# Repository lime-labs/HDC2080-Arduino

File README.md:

Texas Instruments HDC2080 Arduino Library
==========================================
*** NOTE: This library was originally from https://training.ti.com/how-interface-hdc2010-humidity-and-temperature-sensor-arduino-using-i2c
*** This library was originally for the HDC2010 and was converted to support the HDC2080.
*** forked from https://github.com/tinkeringtech/HDC2080_breakout to https://github.com/lime-labs/HDC2080-Arduino for use in the "Lime Labs Hot Slice" temperature and humidity logger project
*** contains fixes and cleanups generously provided by https://github.com/stickbreaker to fix behavior on newer ESP32 Arduino core releases
*** generalized the error handling to restore compatibilty with broader range of MCUs and Arduino cores.

Description: 
	The HDC2080 Library for Arduino allows for configuration and use of 
	the HDC2080 without the need to use I2C or know the register mapping of 
	the device. 
	
	Feel free to modify and reuse this library as you see fit. This code is
	released AS-IS into the public domain. No guarantee or warranty is given.
	This code will not be supported by Texas Instruments after release. 
	
---------------------------------------------------------------------------------------
Installation:
	Extract or copy the HDC2080 Arduino Library folder into the 'libraries'
	folder found in your Arduino Sketchbook. The example sketch will then
	be available under 'custom libraries' when you select File-> Examples.
	
---------------------------------------------------------------------------------------
Contents:
	HDC2080.cpp 		- C++ File defining  behavior of HDC2080 methods
	HDC2080.h   		- Header file for HDC2080.cpp
	keywords.txt		- Keywords from HDC2080.h
	library.properties 	- Properties file for HDC2080 library
	Examples 		- Holds HDC2080 example sketch

----------------------------------------------------------------------------------------

Library Functions:

		HDC2080(uint8_t addr)
			- Initializes an HDC2080 object
			
		void begin(void)  						
			- Equivalent to wire.Begin(), Joins I2C Bus
   
                bool isConnected(void)
		        - Returns true if sensor is connected
			
		float readTemp(void)					
			- Returns the temperature in degrees C
		
		float readHumidity(void)				
			- Returns the relative humidity
		
		void enableHeater(void)				
			- Enables the heating element
		
		void disableHeater(void)
			- Disables the heating element
			
		void setLowTemp(float temp)			
			- Sets the lower temperature threshold (in celcius). Temperature may not
			  be exact due to 8 bit quantization.
			  
		void setHighTemp(float temp)	
			- Sets the upper temperature threshold (in celcius). Temperature may not
			  be exact due to 8 bit quantization.	
			  
		void setHighHumidity(float humid)		
			- Sets the upper humidity threshold (as a %). Humidity may not
			  be exact due to 8 bit quantization.
		
		void setLowHumidity(float humid)	
			- Sets the lower humidity threshold (as a %). Humidity may not
			  be exact due to 8 bit quantization.
	
		float readLowHumidityThreshold(void)	
			- Returns contents of low humidity threshold register
			
		float readHighHumidityThreshold(void)	
			- Returns contents of high humidity threshold register
			
		float readLowTempThreshold(void)		
			- Returns contents of low temperature threshold register (in C)
			
		float readHighTempThreshold(void)
			- Returns contents of high temperature threshold register (in C)
			
		void triggerMeasurement(void)			
			- Triggers a manual temperature/humidity reading. Use to start
			  the taking of regular measurements.
			  
		void reset(void)						
			- Triggers a software reset, all registers are returned to default values
			
		void enableInterrupt(void)				
			- Enables the interrupt/DRDY pin
			
		void disableInterrupt(void)			
			- Disables the interrupt/DRDY pin (High Z)

		uint8_t readInterruptStatus(void)		
			- Reads the status of the interrupt register. The results can be interpreted
			  to know which interrupts have been generated. The HDC2010 datasheet explains
			  the contents of this register.
			  
		void clearMaxTemp(void)			
			- Clears the Maximum temperature register.
			
		void clearMaxHumidity(void)			
			- Clears the Maximum humidity register
			
		float readMaxTemp(void) 				
			- Reads the maximum temperature register
			
		float readMaxHumidity(void)			
			- Reads the maximum humidity register
			
		void enableThresholdInterrupt(void)	
			- Enables high and low temperature/humidity interrupts
			
		void disableThresholdInterrupt(void)	
			- Disables high and low temperature/humidity interrupts
			
		void enableDRDYInterrupt(void)		
			- Enables data ready interrupt
			
		void disableDRDYInterrupt(void)		
			- Disables data ready interrupt
		
		uint8_t readTempOffsetAdjust(void)
			- Returns the offset adjust in binary
		
		uint8_t setTempOffsetAdjust(uint8_t)
			- Set and return the offset adjust in binary

		uint8_t readHumidityOffsetAdjust(void)
			- Returns the offset adjust in binary

		uint8_t setHumidityOffsetAdjust(uint8_t)
			- Set and return the offset adjust in binary

		void setTempRes(int resolution)		
		void setHumidRes(int resolution)	
		   Sets Temperature & Humidity Resolution, 3 options
		   0 - 14 bit
		   1 - 11 bit
		   2 - 9 bit
		   default - 14 bit	

		void setTempRes(int resolution)		
		void setHumidRes(int resolution)	
		   Sets Temperature & Humidity Resolution, 3 options
		   0 - 14 bit
		   1 - 11 bit
		   2 - 9 bit
		   default - 14 bit	

		void setMeasurementMode(int mode)
		   Sets measurement mode, 3 options
		   0 - Temperature and Humidity
		   1 - Temperature only
		   2 - Humidity only
		   default - Temperature & Humidity	

		void setRate(int rate)
		   Sets reading rate, 8 options
		   0 - Manual
		   1 - reading every 2 minutes
		   2 - reading every minute
		   3 - reading every ten seconds
		   4 - reading every 5 seconds
		   5 - reading every second
		   6 - reading at 2Hz
		   7 - reading at 5Hz
		   default - Manual			

		void setInterruptPolarity(int polarity)
		   Sets Interrupt polarity, 2 options
		   0 - Active Low
		   1 - Active High
		   default - Active Low		

		void setInterruptMode(int polarity)
		   Sets Interrupt mode, 2 options
		   0 - Level sensitive
		   1 - Comparator mode
		   default - Level sensitive

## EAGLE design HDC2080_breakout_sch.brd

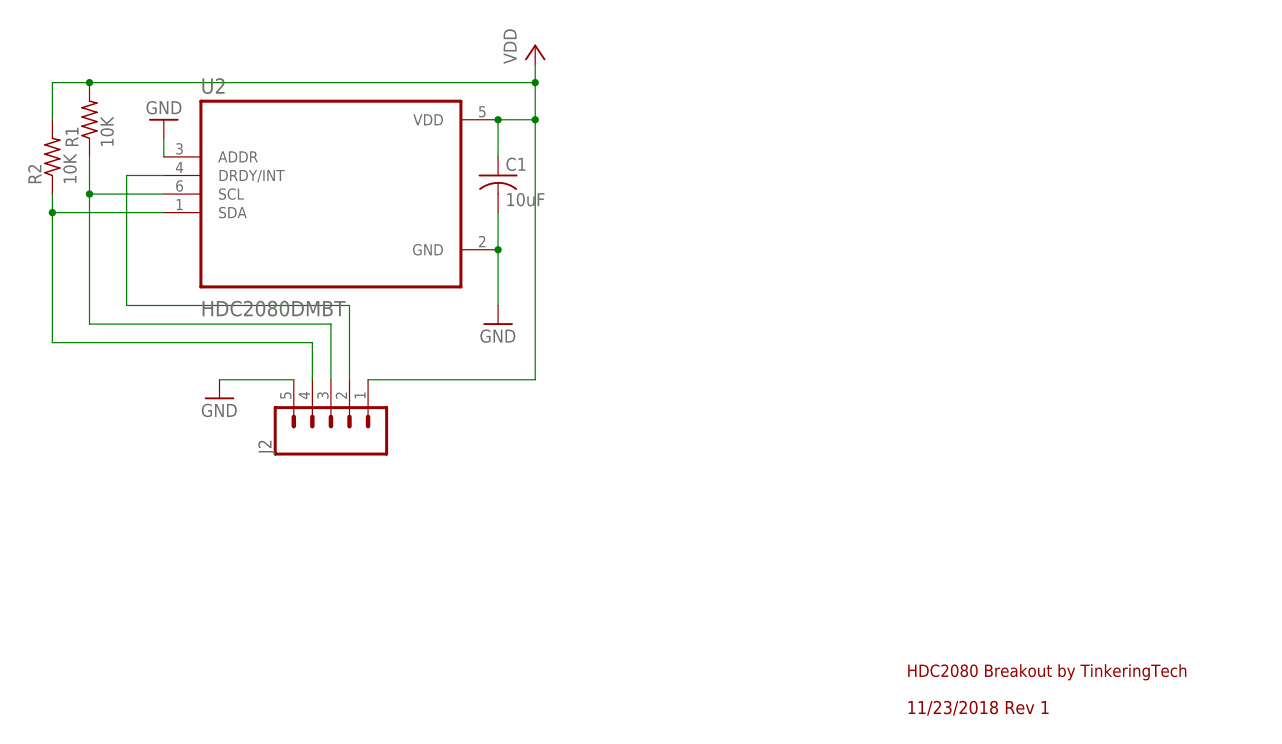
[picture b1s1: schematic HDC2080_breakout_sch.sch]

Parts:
C1: 10uF; C0402
J2: CONN_05; 1X05
R1, R2: 10K; R0402
U2: HDC2080DMBT; SON100P300X300X80-7N

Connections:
GND: C1.2, J2.5, U2.2 (GND), U2.3 (ADDR)
unnamed: J2.3, R1.1, U2.6 (SCL)
unnamed: J2.4, R2.1, U2.1 (SDA)
unnamed: J2.2, U2.4 (DRDY/INT)
VCC: C1.1, J2.1, R1.2, R2.2, U2.5 (VDD)

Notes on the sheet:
HDC2080 Breakout by TinkeringTech
11/23/2018 Rev 1

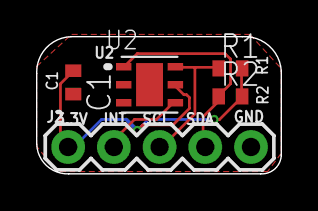
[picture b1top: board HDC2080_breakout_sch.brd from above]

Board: 2 copper layers, 13.6 x 7.6 mm, 5 parts (0 on the bottom side), 5 nets.

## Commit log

2024-02-13 Add description to isConnected
2024-11-07 Temperature equation update
2024-11-07 float numbers

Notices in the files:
parts and their libraries:
SparkFun-Connectors: Licensing: Creative Commons ShareAlike 4.0 International - https://creativecommons.org/licenses/by-sa/4.0
